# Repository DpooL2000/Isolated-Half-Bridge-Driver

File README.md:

# Isolated Half-Bridge Motor Driver

A robust, single half-bridge motor driver featuring galvanic PWM isolation and high-resolution bidirectional current sensing. Designed to safely interface a microcontroller with high-voltage motor rails while providing precise analog current feedback.

## Project Status
- **Hardware:** Complete (KiCad schematic and PCB layout finalized).
- **Firmware:** C++ driver code currently in development.

## Key Hardware Specifications
* **Gate Driver:** IR2101 with bootstrap topology (1N5819 diode / 1uF cap).
* **Power Stage:** 2x IRFZ44N N-Channel MOSFETs with 1000uF bulk smoothing.
* **Galvanic Isolation:** 2x 6N137 high-speed optocouplers protecting the logic side.
* **Current Sensing:** AD8418 bidirectional amplifier across an R002 milliohm shunt, heavily filtered (10Ω/10nF/1nF).
* **Reference Voltage:** Buffered 1.65V rail generated via MCP6002 for center-biased bidirectional sensing.

## Interface & Pinout

### Logic Side (Low Voltage)
* **PWM_H / PWM_L:** 2-Channel high-speed logic inputs (isolated via 6N137).
* **I_SENSE_OUT:** Amplified analog voltage representing motor current (centered at 1.65V).
* **VCC_LOGIC:** Input for the onboard LDO stepping down to power the opto-secondaries and IR2101.
* **GND:** Logic ground.

### Power Side (High Voltage)
* **MOTOR_V+:** Main high-voltage power rail.
* **MOTOR_OUT:** Half-bridge switching output to the motor.
* **GND_PWR:** Power ground (isolated from logic ground).

## Repository Structure
* `/Hardware` - KiCad project files (`.kicad_pro`, `.kicad_sch`, `.kicad_pcb`).
* `/Docs` - PDF schematics, board renders, and full CSV Bill of Materials.
* `/Firmware` - Placeholder for the upcoming C++ hardware abstraction and control classes. 

## Usage Notes
The design utilizes a bootstrap capacitor (C3) for the high-side MOSFET. The low-side MOSFET must be periodically pulsed on to recharge the bootstrap capacitor; do not attempt 100% duty cycle on the high side.

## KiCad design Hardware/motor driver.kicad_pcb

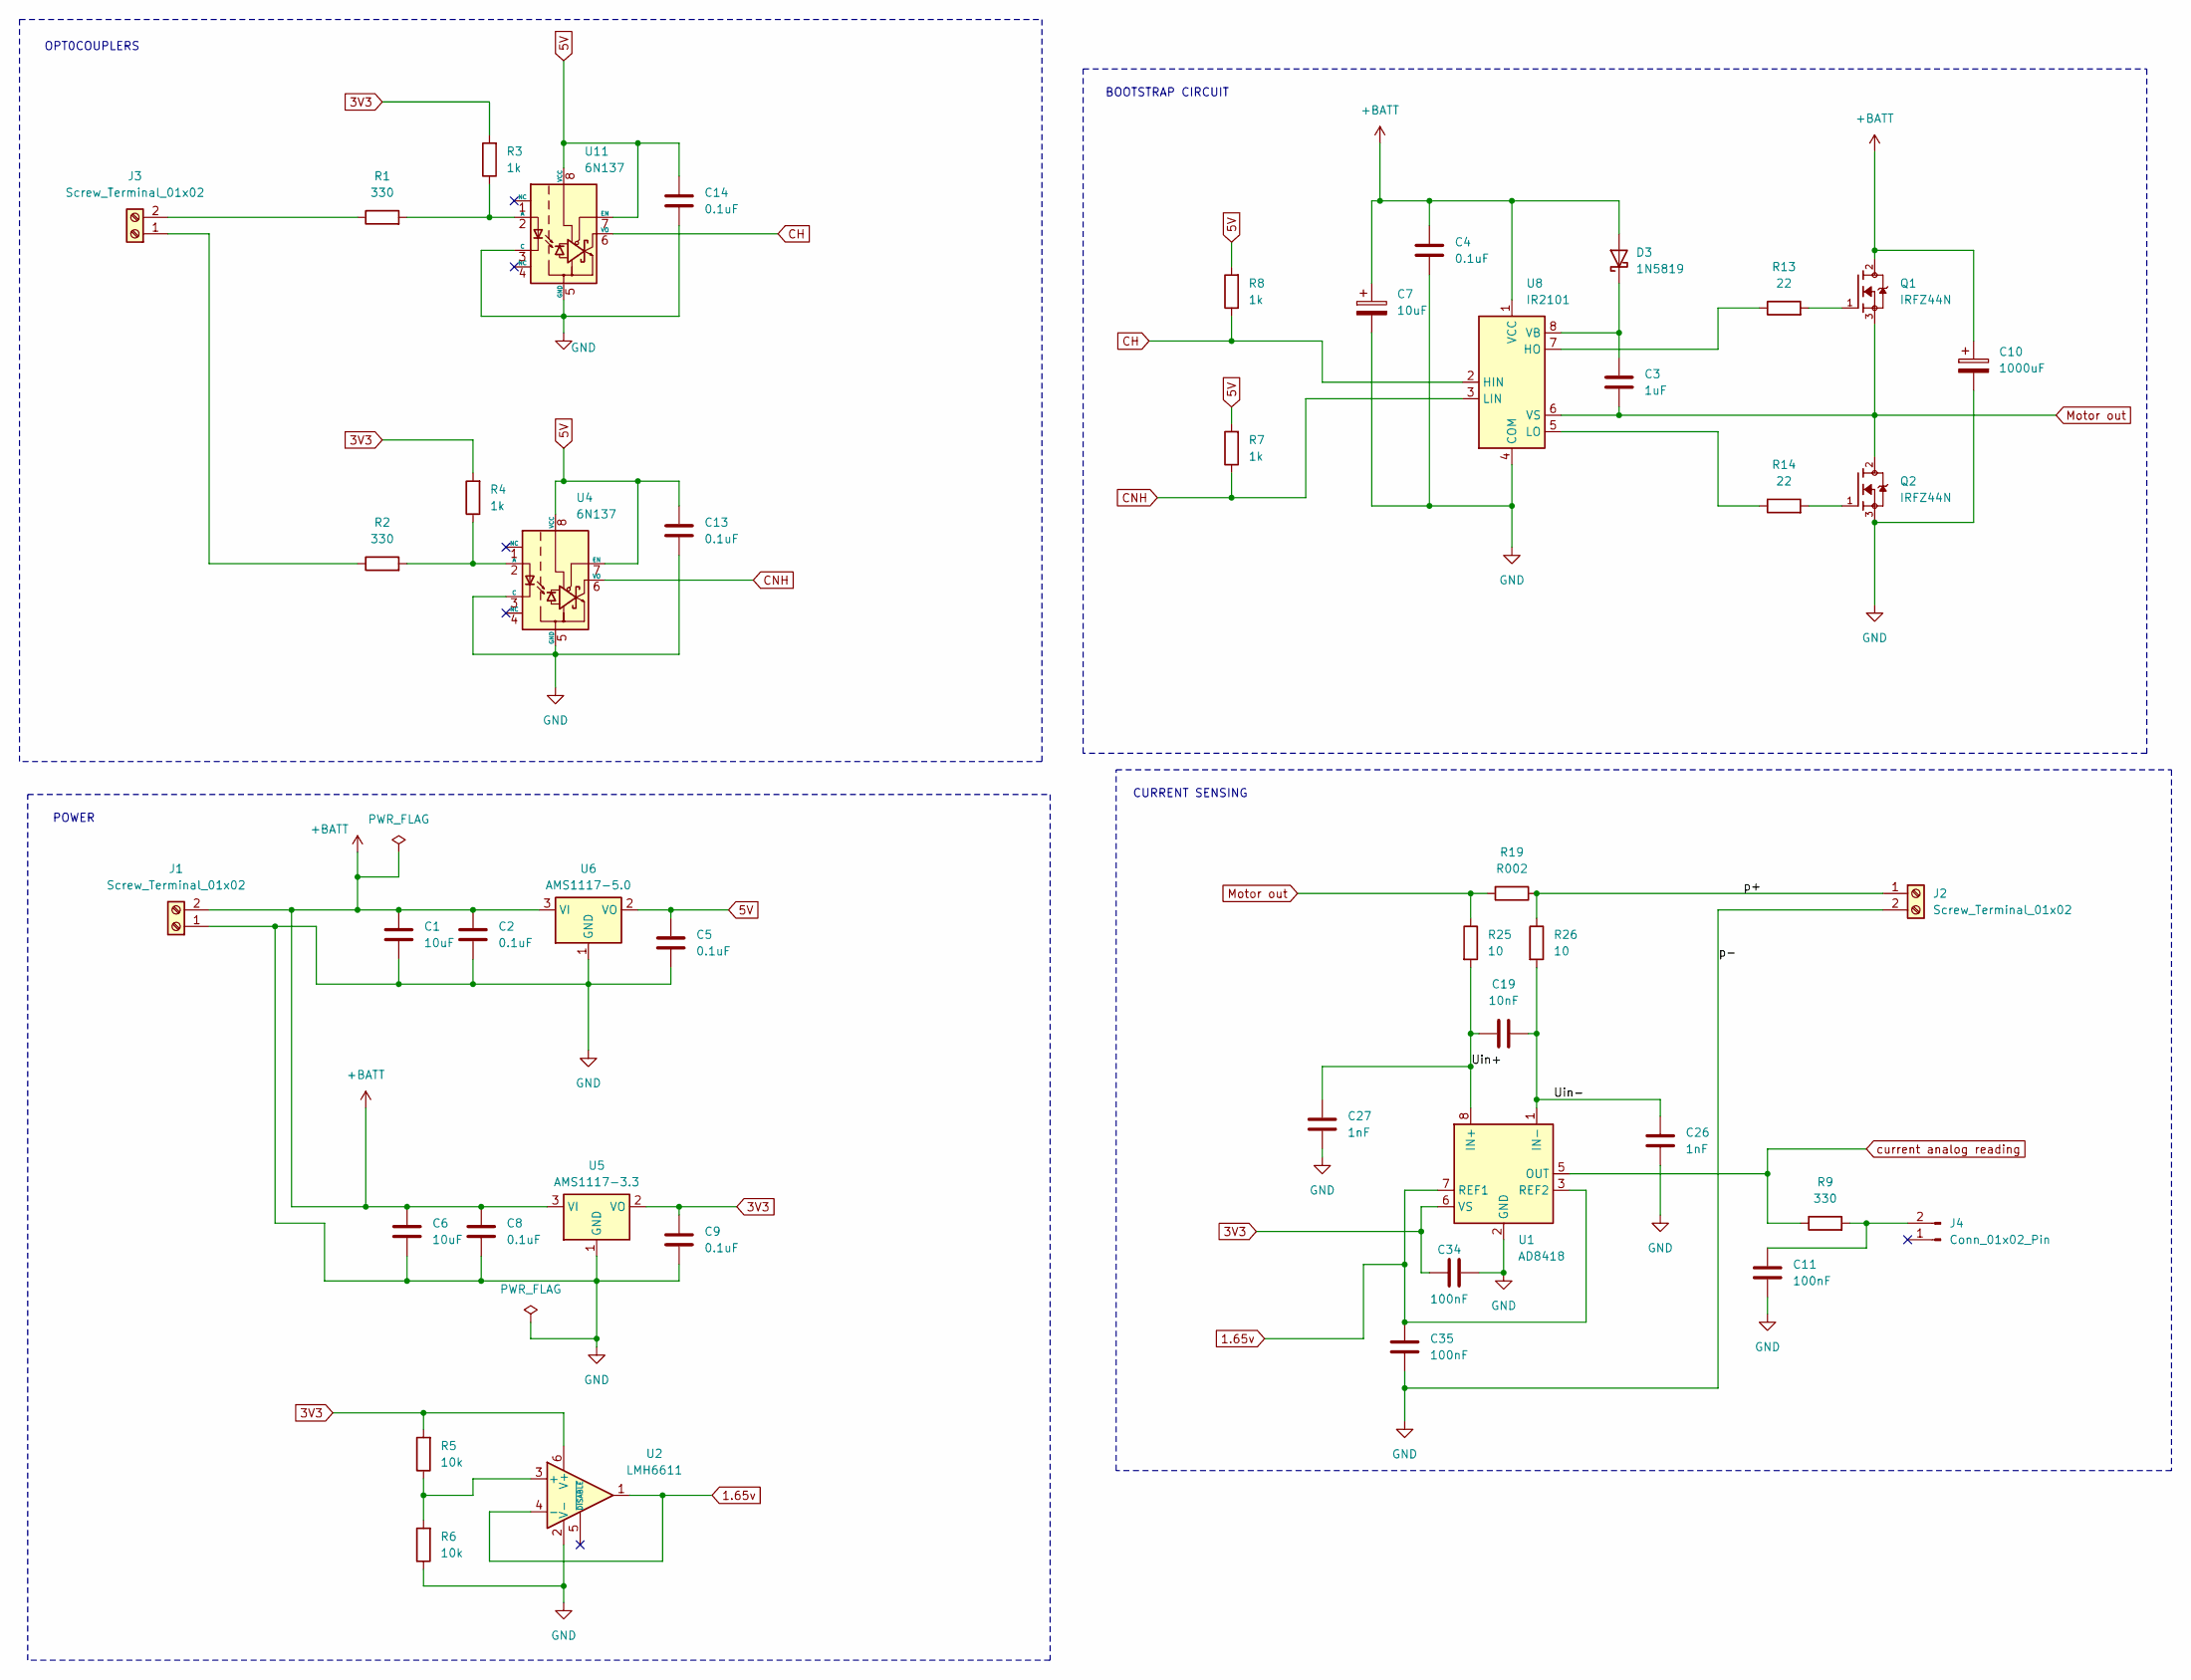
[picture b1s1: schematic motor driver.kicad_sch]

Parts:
C1, C6: 10uF; C_Disc_D3.0mm_W2.0mm_P2.50mm
C2, C4, C5, C8, C9, C13, C14: 0.1uF; C_Disc_D3.0mm_W2.0mm_P2.50mm
C3: 1uF; C_Disc_D3.0mm_W2.0mm_P2.50mm
C7: 10uF; C_Radial_D5.0mm_H5.0mm_P2.00mm
C10: 1000uF; CP_Radial_D10.0mm_P5.00mm
C11, C34, C35: 100nF; C_Disc_D3.0mm_W2.0mm_P2.50mm
C19: 10nF; C_Disc_D3.0mm_W2.0mm_P2.50mm
C26, C27: 1nF; C_Disc_D3.0mm_W2.0mm_P2.50mm
D3: 1N5819; D_DO-41_SOD81_P2.54mm_Vertical_AnodeUp
J1, J2: Screw_Terminal_01x02; TerminalBlock_MaiXu_MX126-5.0-02P_1x02_P5.00mm
J3: Screw_Terminal_01x02; TerminalBlock_Xinya_XY308-2.54-2P_1x02_P2.54mm_Horizontal
J4: Conn_01x02_Pin; PinHeader_1x02_P2.54mm_Vertical
Q1, Q2: IRFZ44N; TO-220-3_Vertical; PARTREV 09/21/10
R1, R2, R9: 330; R_Axial_DIN0204_L3.6mm_D1.6mm_P1.90mm_Vertical
R3, R4, R7, R8: 1k; R_Axial_DIN0204_L3.6mm_D1.6mm_P1.90mm_Vertical
R5, R6: 10k; R_Axial_DIN0204_L3.6mm_D1.6mm_P1.90mm_Vertical
R13, R14: 22; R_Axial_DIN0204_L3.6mm_D1.6mm_P1.90mm_Vertical
R19: R002; R_4020_10251Metric
R25, R26: 10; R_Axial_DIN0204_L3.6mm_D1.6mm_P1.90mm_Vertical
U1: AD8418; SOIC-8_3.9x4.9mm_P1.27mm
U2: LMH6611; TSOT-23-6
U4, U11: 6N137; DIP-8_W7.62mm
U5: AMS1117-3.3; SOT-223-3_TabPin2
U6: AMS1117-5.0; SOT-223-3_TabPin2
U8: IR2101; DIP-8_W7.62mm_LongPads

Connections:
1.65v: C35.1, U1.3 (REF2), U1.7 (REF1), U2.1, U2.4 (-)
3V3: C9.1, C34.2, R3.2, R4.2, R5.2, U1.6 (VS), U2.6 (V+), U5.2 (VO)
5V: C5.1, C13.1, C14.1, R7.2, R8.2, U4.7 (EN), U4.8 (VCC), U6.2 (VO), U11.7 (EN), U11.8 (VCC)
+BATT: C1.1, C2.1, C4.1, C6.1, C7.1, C8.1, C10.1, D3.2 (A), J1.2, Q1.2, U5.3 (VI), U6.3 (VI), U8.1 (VCC)
/Uin+: C19.2, C27.1, R25.2, U1.8 (IN+)
/Uin-: C19.1, C26.1, R26.2, U1.1 (IN-)
/p+: J2.1, R19.1, R26.1
CH: R8.1, U8.2 (HIN), U11.6 (VO)
CNH: R7.1, U4.6 (VO), U8.3 (LIN)
GND: C1.2, C2.2, C4.2, C5.2, C6.2, C7.2, C8.2, C9.2, C10.2, C11.1, C13.2, C14.2, C26.2, C27.2, C34.1, C35.2, J1.1, J2.2, Q2.3, R6.1, U1.2 (GND), U2.2 (V-), U4.3 (C), U4.5 (GND), U5.1 (GND), U6.1 (GND), U8.4 (COM), U11.3 (C), U11.5 (GND)
Motor out: C3.2, Q1.3, Q2.2, R19.2, R25.1, U8.6 (VS)
unnamed: C3.1, D3.1 (K), U8.8 (VB)
unnamed: J3.1, R2.1
unnamed: J3.2, R1.1
unnamed: C11.2, J4.2, R9.2
unnamed: Q1.1, R13.2
unnamed: Q2.1, R14.2
unnamed: R5.1, R6.2, U2.3 (+)
unnamed: R2.2, R4.1, U4.2 (A)
unnamed: R13.1, U8.7 (HO)
unnamed: R14.1, U8.5 (LO)
unnamed: R1.2, R3.1, U11.2 (A)
current analog reading: R9.1, U1.5 (OUT)

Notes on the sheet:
OPT0COUPLERS
CURRENT SENSING
POWER
BOOTSTRAP CIRCUIT

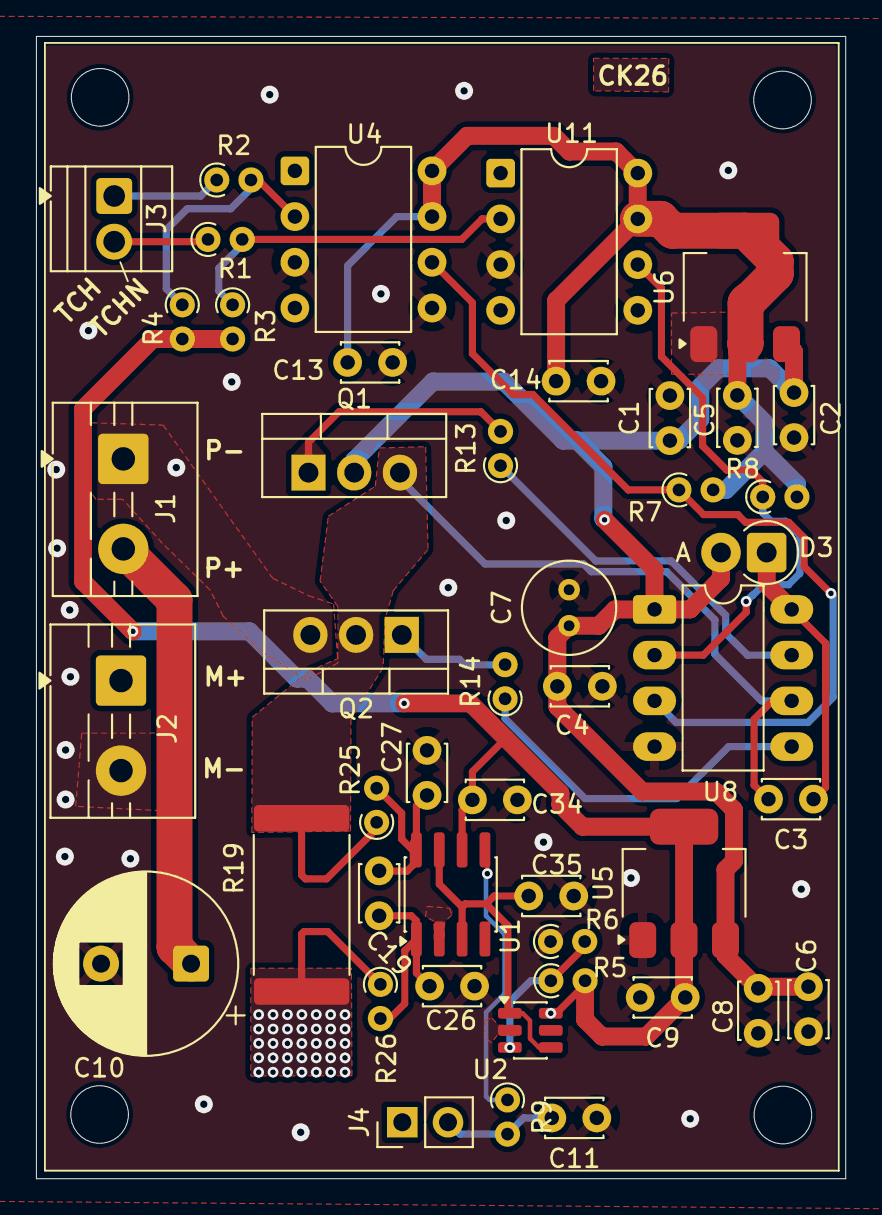
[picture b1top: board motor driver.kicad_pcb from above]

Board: 2 copper layers, 45.0 x 63.5 mm, 46 parts (0 on the bottom side), 23 nets.
